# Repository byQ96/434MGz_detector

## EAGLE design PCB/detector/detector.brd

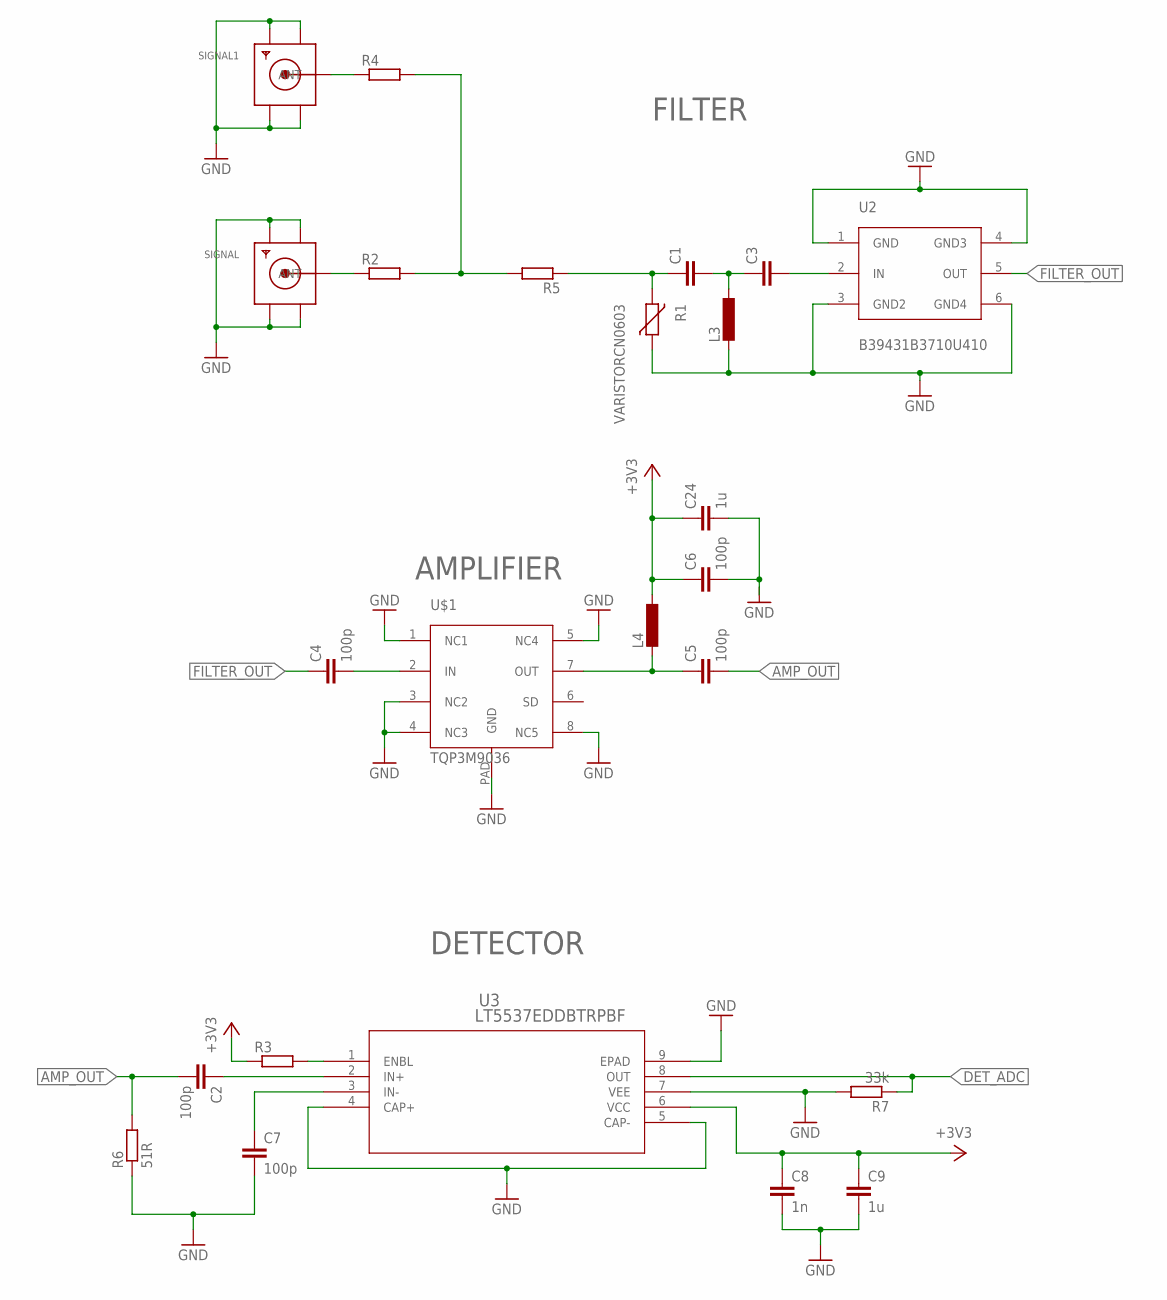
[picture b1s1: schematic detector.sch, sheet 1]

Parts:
C1, C3: C-EUC0603; C0603
C2, C4, C5, C6, C7: 100p; C0603
C8: 1n; C0603
C9, C24: 1u; C0603
L3, L4: L-EUL2012C; L2012C
R1: VARISTORCN0603; CT/CN0603
R2, R3, R4, R5: R-EU_R0603; R0603
R6: 51R; R0603
R7: 33k; R0603
SIGNAL, SIGNAL1: SMACONNECTOR_EDGE; SMA_EDGELAUNCH
U2: B39431B3710U410; SON120P300X300X110-6N
U3: LT5537EDDBTRPBF; DFN-8_DDB
U$1: TQP3M9036; DFN-8_2X2

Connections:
+3V3: C6.1, C8.1, C9.1, C24.1, L4.1, R3.1, U3.6 (VCC); also elsewhere on the board
AMP_OUT: C2.2, C5.2, R6.2
DET_ADC: R7.1, U3.8 (OUT); also elsewhere on the board
FILTER_IN: C3.2, U2.2 (IN)
FILTER_OUT: C4.1, U2.5 (OUT)
GND: C6.2, C7.2, C8.2, C9.2, C24.2, L3.2, R1.1, R6.1, R7.2, SIGNAL.GND@1 (GND4), SIGNAL.GND@2 (GND3), SIGNAL.GND@3 (GND2), SIGNAL.GND@4 (GND1), SIGNAL1.GND@1 (GND4), SIGNAL1.GND@2 (GND3), SIGNAL1.GND@3 (GND2), SIGNAL1.GND@4 (GND1), U2.1 (GND), U2.3 (GND2), U2.4 (GND3), U2.6 (GND4), U3.4 (CAP+), U3.5 (CAP-), U3.7 (VEE), U3.9 (EPAD), U$1.1 (NC1), U$1.3 (NC2), U$1.4 (NC3), U$1.5 (NC4), U$1.8 (NC5), U$1.PAD (GND); also elsewhere on the board
unnamed: R3.2, U3.1 (ENBL)
unnamed: C7.1, U3.3 (IN-)
unnamed: C2.1, U3.2 (IN+)
unnamed: R2.1, SIGNAL.P (ANT)
unnamed: C1.2, C3.1, L3.1
unnamed: R4.1, SIGNAL1.P (ANT)
unnamed: C4.2, U$1.2 (IN)
unnamed: C5.1, L4.2, U$1.7 (OUT)
SIGNAL: C1.1, R1.2, R5.1
SIGNAL1: R2.2, R4.2, R5.2

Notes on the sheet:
DETECTOR
FILTER
AMPLIFIER

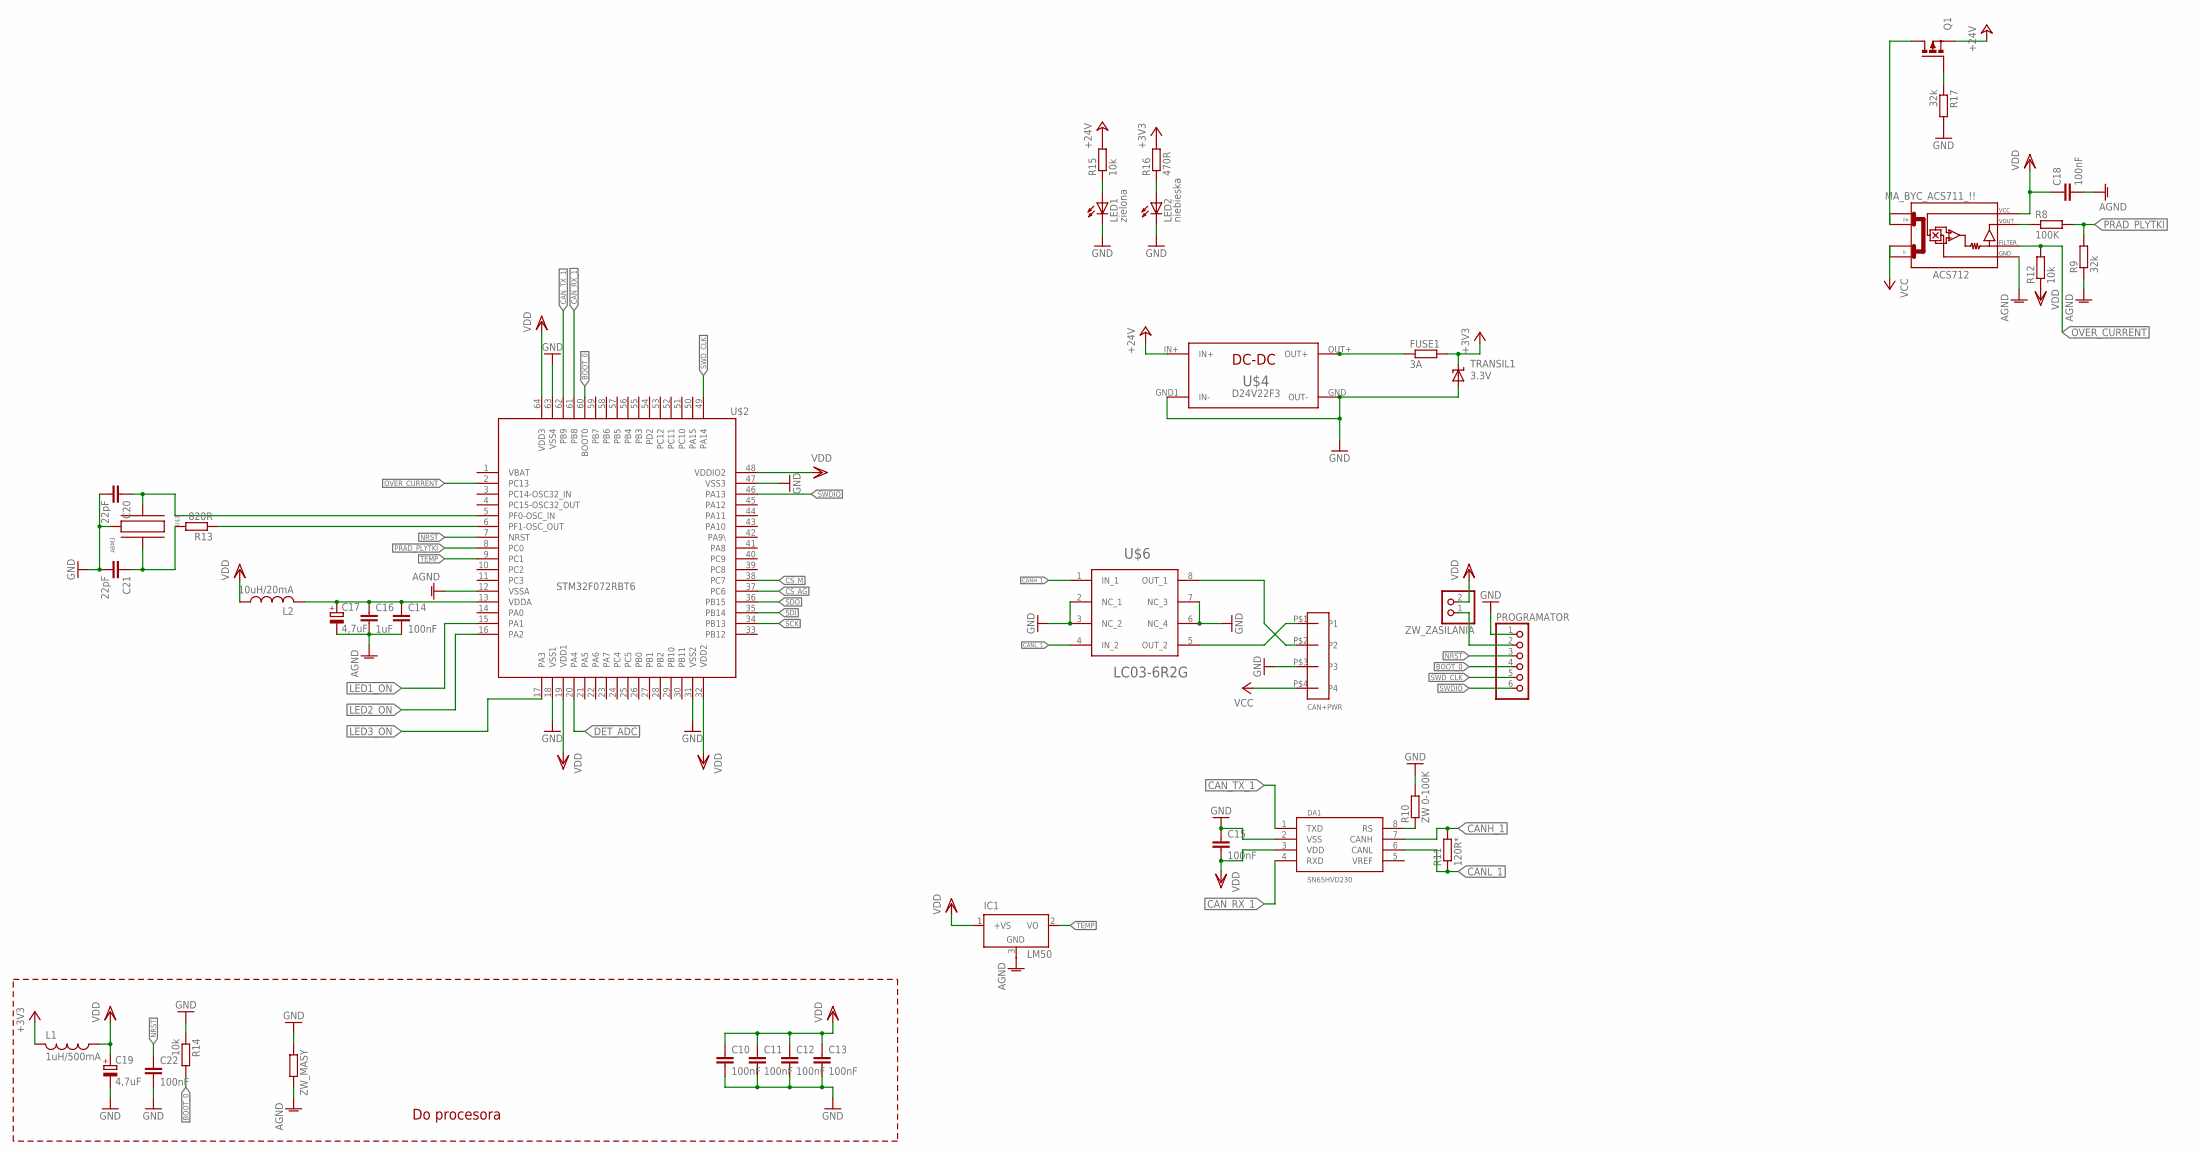
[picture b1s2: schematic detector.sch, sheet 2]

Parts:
C10, C11, C12, C13, C14, C15, C18, C22: 100nF; C0603
C16: 1uF; C0603
C17, C19: 4,7uF; SMC_A
C20, C21: 22pF; C0603
CAN+PWR: 4PIN_3.81_KATOWA; CON-PHOENIX_3.81-4PIN_KAT
DA1: SN65HVD230; SO08
FUSE1: 3A; R0603
IC1: LM50; SOT23
L1: 1uH/500mA; L2012C
L2: 10uH/20mA; L2012C
LED1: zielona; CHIP-LED0603
LED2: niebieska; CHIP-LED0603
MA_BYC_ACS711_!!: ACS712; SO08
PROGRAMATOR: PINHD-1X6; 1X06
Q1: P-MOSFET-SO8; SO-08
R8: 100K; R0603
R9, R17: 32k; R0603
R10: ZW 0-100K; R0603
R11: 120R*; R0603
R12, R14, R15: 10k; R0603
R13: 820R; R0603
R16: 470R; R0603
TRANSIL1: 3.3V; SMBJ
U$2: STM32F072RBT6; TQFP64
U$3: ABM3
U$4: D24V22F3
U$6: LC03-6R2G; SOIC-8
ZW_MASY: R-EU_R0603; R0603
ZW_ZASILANIA: PINHD-1X2; 1X02

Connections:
+3V3: FUSE1.2, L1.2, R16.2, TRANSIL1.C; also elsewhere on the board
+24V: Q1.1 (S), Q1.2 (S), Q1.3 (S), R15.2, U$4.IN+
AGND: C14.2, C16.2, C17.-, C18.2, IC1.3 (GND), MA_BYC_ACS711_!!.5 (GND), R9.1, U$2.12 (VSSA), ZW_MASY.2
BOOT_0: PROGRAMATOR.4, R14.2, U$2.60 (BOOT0)
CANH_1: DA1.7 (CANH), R11.2, U$6.1 (IN_1)
CANL_1: DA1.6 (CANL), R11.1, U$6.4 (IN_2)
CAN_RX_1: DA1.4 (RXD), U$2.61 (PB8)
CAN_TX_1: DA1.1 (TXD), U$2.62 (PB9)
CS_AG: U$2.37 (PC6); also elsewhere on the board
CS_M: U$2.38 (PC7); also elsewhere on the board
DET_ADC: U$2.20 (PA4); also elsewhere on the board
GND: C10.2, C11.2, C12.2, C13.2, C15.1, C19.-, C20.2, C21.2, C22.2, CAN+PWR.P$3 (P3), DA1.2 (VSS), LED1.C, LED2.C, PROGRAMATOR.1, R10.2, R14.1, R17.2, TRANSIL1.A, U$2.18 (VSS1), U$2.31 (VSS2), U$2.47 (VSS3), U$2.63 (VSS4), U$3.P$1, U$3.P$3, U$4.GND (OUT-), U$4.GND1 (IN-), U$6.2 (NC_1), U$6.3 (NC_2), U$6.6 (NC_4), U$6.7 (NC_3), ZW_MASY.1; also elsewhere on the board
LED1_ON: U$2.15 (PA1)
LED2_ON: U$2.16 (PA2)
LED3_ON: U$2.17 (PA3)
unnamed: MA_BYC_ACS711_!!.7 (VOUT), R8.1
unnamed: DA1.8 (RS), R10.1
unnamed: FUSE1.1, U$4.OUT+
unnamed: MA_BYC_ACS711_!!.1 (I+_0), MA_BYC_ACS711_!!.2 (I+_1), Q1.5 (D), Q1.6 (D), Q1.7 (D), Q1.8 (D)
unnamed: R13.1, U$2.6 (PF1-OSC_OUT)
unnamed: C20.1, U$2.5 (PF0-OSC_IN), U$3.P$2
unnamed: C14.1, C16.1, C17.+, L2.2, U$2.13 (VDDA)
unnamed: C21.1, R13.2, U$3.P$4
unnamed: CAN+PWR.P$2 (P2), U$6.8 (OUT_1)
unnamed: CAN+PWR.P$1 (P1), U$6.5 (OUT_2)
unnamed: LED1.A, R15.1
unnamed: LED2.A, R16.1
unnamed: Q1.4 (G), R17.1
unnamed: PROGRAMATOR.2, ZW_ZASILANIA.1
NRST: C22.1, PROGRAMATOR.3, U$2.7 (NRST)
OVER_CURRENT: MA_BYC_ACS711_!!.6 (FILTER), R12.2, U$2.2 (PC13)
PRAD_PLYTKI: R8.2, R9.2, U$2.8 (PC0)
SCK: U$2.34 (PB13); also elsewhere on the board
SDI: U$2.35 (PB14); also elsewhere on the board
SDO: U$2.36 (PB15); also elsewhere on the board
SWDIO: PROGRAMATOR.6, U$2.46 (PA13)
SWD_CLK: PROGRAMATOR.5, U$2.49 (PA14)
TEMP: IC1.2 (VO), U$2.9 (PC1)
VCC: CAN+PWR.P$4 (P4), MA_BYC_ACS711_!!.3 (I-_0), MA_BYC_ACS711_!!.4 (I-_1)
VDD: C10.1, C11.1, C12.1, C13.1, C15.2, C18.1, C19.+, DA1.3 (VDD), IC1.1 (+VS), L1.1, L2.1, MA_BYC_ACS711_!!.8 (VCC), R12.1, U$2.19 (VDD1), U$2.32 (VDD2), U$2.48 (VDDIO2), U$2.64 (VDD3), ZW_ZASILANIA.2

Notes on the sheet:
Do procesora

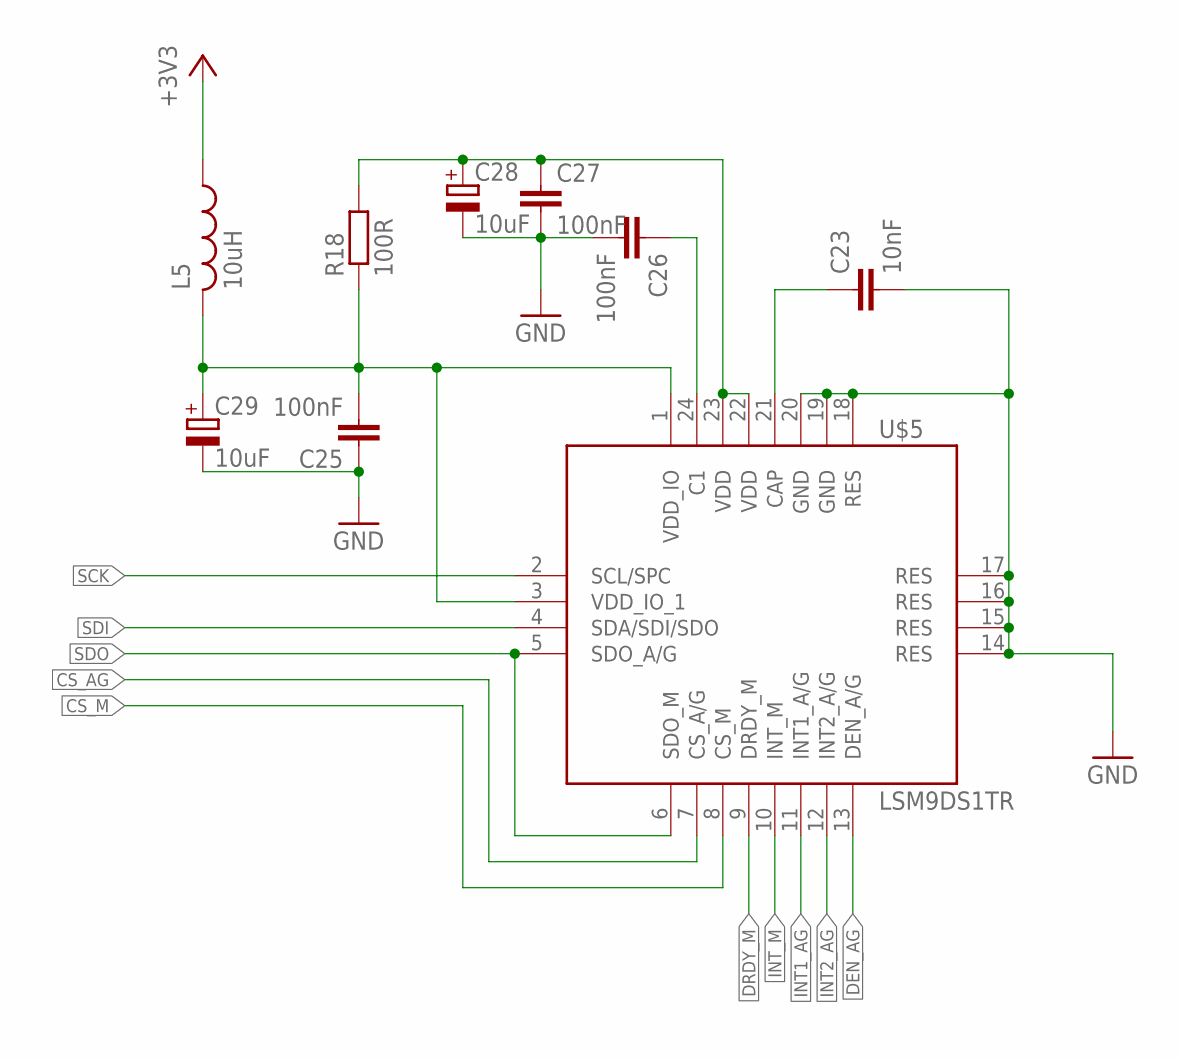
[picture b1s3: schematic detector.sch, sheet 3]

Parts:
C23: 10nF; C0603
C25, C26, C27: 100nF; C0603
C28, C29: 10uF; SMC_A
L5: 10uH; L2012C
R18: 100R; R0603
U$5: LSM9DS1TR; LGA24

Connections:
+3V3: L5.1; also elsewhere on the board
CS_AG: U$5.7 (CS_A/G); also elsewhere on the board
CS_M: U$5.8 (CS_M); also elsewhere on the board
DEN_AG: U$5.13 (DEN_A/G)
DRDY_M: U$5.9 (DRDY_M)
GND: C23.2, C25.1, C26.2, C27.2, C28.-, C29.-, U$5.14 (RES), U$5.15 (RES), U$5.16 (RES), U$5.17 (RES), U$5.18 (RES), U$5.19 (GND), U$5.20 (GND); also elsewhere on the board
INT1_AG: U$5.11 (INT1_A/G)
INT2_AG: U$5.12 (INT2_A/G)
INT_M: U$5.10 (INT_M)
unnamed: C27.1, C28.+, R18.2, U$5.22 (VDD), U$5.23 (VDD)
unnamed: C23.1, U$5.21 (CAP)
unnamed: C26.1, U$5.24 (C1)
unnamed: C25.2, C29.+, L5.2, R18.1, U$5.1 (VDD_IO), U$5.3 (VDD_IO_1)
SCK: U$5.2 (SCL/SPC); also elsewhere on the board
SDI: U$5.4 (SDA/SDI/SDO); also elsewhere on the board
SDO: U$5.5 (SDO_A/G), U$5.6 (SDO_M); also elsewhere on the board

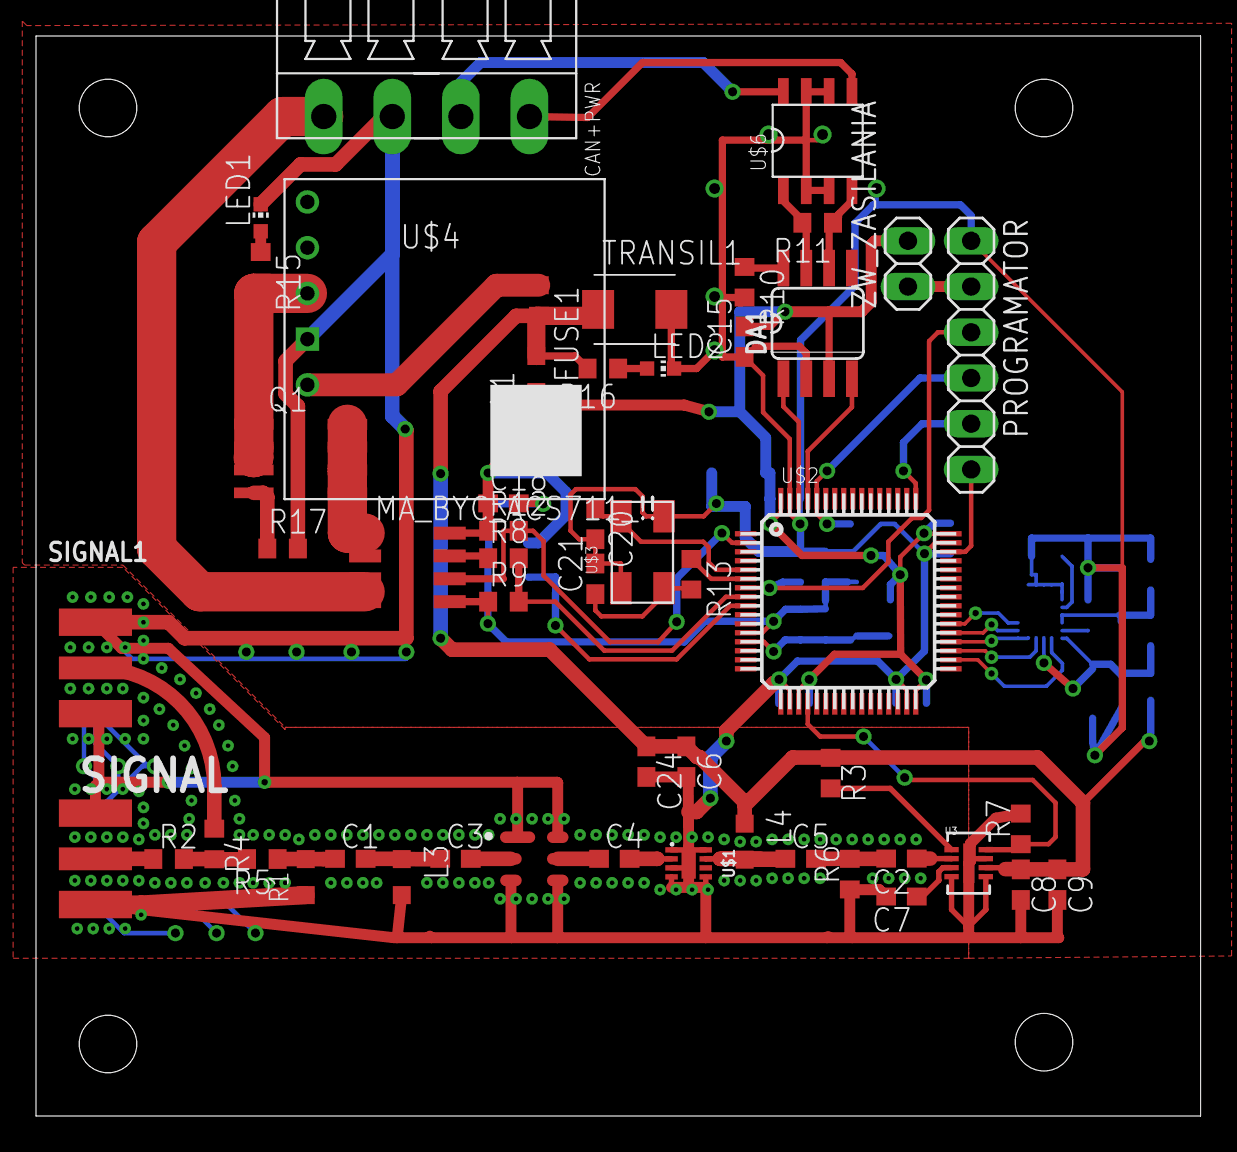
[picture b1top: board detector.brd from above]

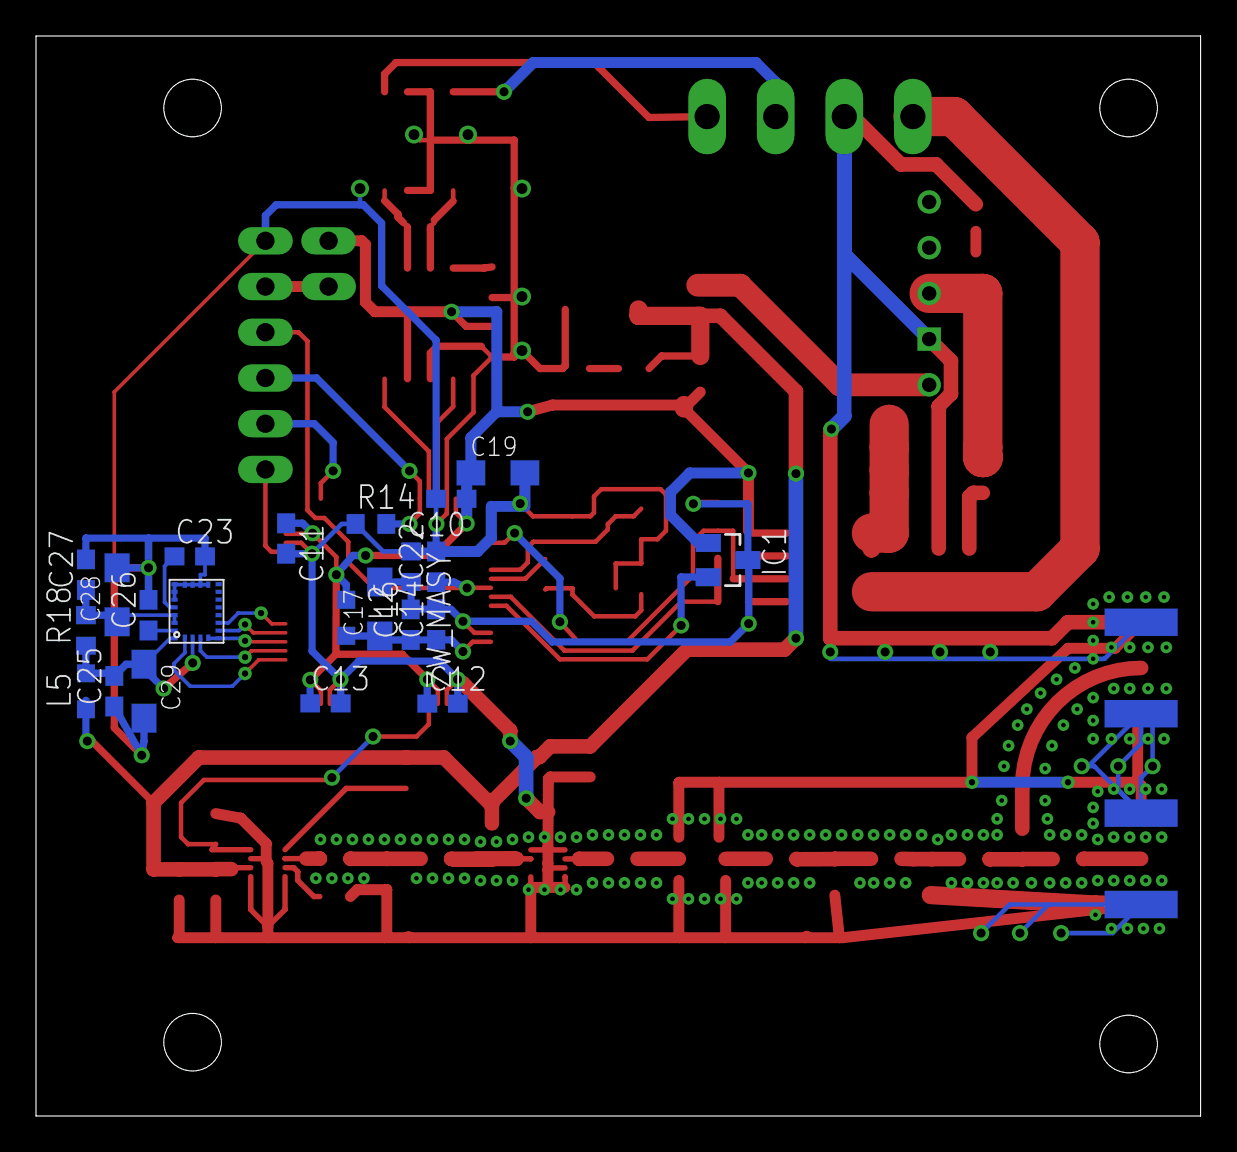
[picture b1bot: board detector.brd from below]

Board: 2 copper layers, 64.7 x 60.0 mm, 74 parts (22 on the bottom side), 54 nets.

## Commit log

2018-05-04 detector ready
2018-06-06 almost ready
2018-06-07 signal gap and vias to add
2018-06-09 rf circut edited, pololu lbr added
2018-06-17 reinstall
2018-06-30 first connection commit
2018-07-01 imu added
